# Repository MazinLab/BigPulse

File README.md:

# BigPulse
A high power avalanche mode laser driver

For fully isolated use, cut the jumper on the bottom, do not populate the boost converter and supply 200V and 12V to each side seperately

For use without ground isolation do not populate anything on the bottom other than the sense resistors and supply 12V through the barrel jack

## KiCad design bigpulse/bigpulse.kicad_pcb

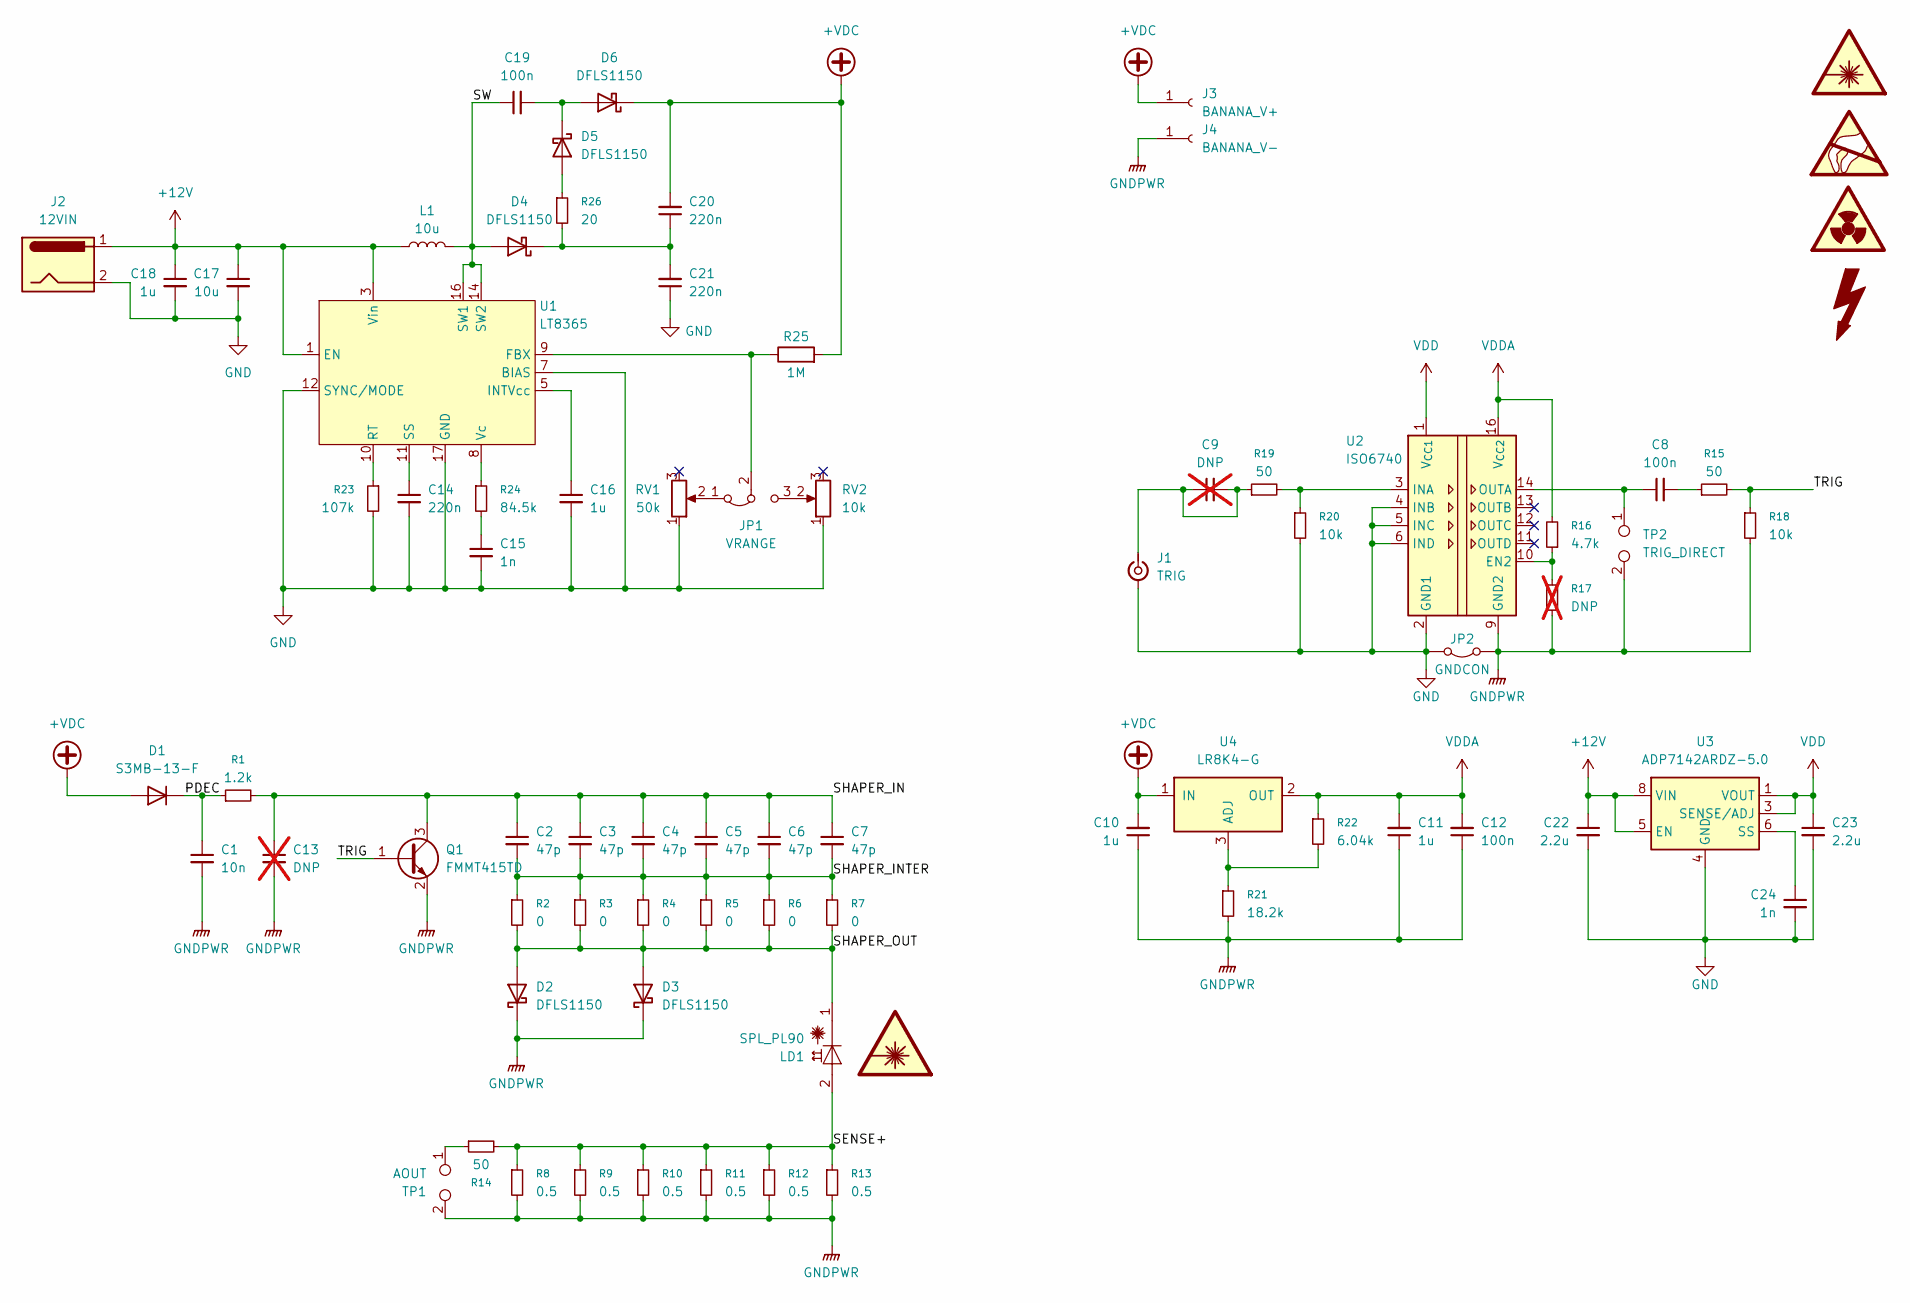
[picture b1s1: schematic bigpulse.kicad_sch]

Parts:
C1: 10n; C_1210_3225Metric; DIGIKEY_PN 709-VPDF102W103K1GV001ECT-ND
C2, C3, C4, C5, C6, C7: 47p; C_1210_3225Metric; DIGIKEY_PN 720-1040-1-ND
C8, C12, C19: 100n; C_1210_3225Metric; DIGIKEY_PN 445-2300-1-ND
C9: DNP; C_0603_1608Metric; not fitted
C10, C18: 1u; C_2220_5750Metric; DIGIKEY_PN 478-KGF55DR72J105KVCT-ND
C11, C16: 1u; C_0603_1608Metric; DIGIKEY_PN 1276-1946-1-ND
C13: DNP; C_1210_3225Metric; not fitted
C14: 220n; C_0603_1608Metric; DIGIKEY_PN 490-5402-1-ND
C15, C24: 1n; C_0603_1608Metric; DIGIKEY_PN 399-C0603C102K5RACTUCT-ND
C17: 10u; C_2220_5750Metric; DIGIKEY_PN 478-KGM55DR72A106MVCT-ND
C20, C21: 220n; C_2220_5750Metric; DIGIKEY_PN 490-3520-1-ND
C22, C23: 2.2u; C_0603_1608Metric; DIGIKEY_PN 490-GRM188Z71E225ME43DCT-ND
D1: S3MB-13-F; D_SMB; DIGIKEY_PN S3MB-FDICT-ND
D2, D3, D4, D5, D6: DFLS1150; D_PowerDI-123; DIGIKEY_PN DFLS1150Q-7DICT-ND
J1: TRIG; SMA_Amphenol_132134-10_Vertical; DIGIKEY_PN 132134-10
J2: 12VIN; BarrelJack_Wuerth_694106106102_2.0x5.5mm; DIGIKEY_PN 732-5929-1-ND
J3: BANANA_V+; MountingHole_3.7mm_Pad_Via; DIGIKEY_PN J10125-ND
J4: BANANA_V-; MountingHole_3.7mm_Pad_Via; DIGIKEY_PN J10126-ND
JP1: VRANGE; SolderJumper-3_P1.3mm_Bridged2Bar12_Pad1.0x1.5mm
JP2: GNDCON; SolderJumper-2_P1.3mm_Bridged_Pad1.0x1.5mm
L1: 10u; L_Wurth_WE-LQSH-4020; DIGIKEY_PN 732-3336-1-ND
LD1: SPL_PL90; LED_D5.0mm; DIGIKEY_PN 475-SPLPL90AT03-ND
Q1: FMMT415TD; SOT-23-3; DIGIKEY_PN FMMT415TDCT-ND
R1: 1.2k; R_1210_3225Metric; DIGIKEY_PN 2019-RK73B2ETTD122JCT-ND
R2, R3, R4, R5, R6, R7: 0; R_1210_3225Metric; DIGIKEY_PN RMCF1210ZT0R00CT-ND
R8, R9, R10, R11, R12, R13: 0.5; R_1210_3225Metric; DIGIKEY_PN 311-0.5NACT-ND
R14, R15, R19: 50; R_0603_1608Metric; DIGIKEY_PN 764-FC0603E50R0BTBST1CT-ND
R16: 4.7k; R_0603_1608Metric; DIGIKEY_PN 311-4.70KHRCT-ND
R17: DNP; R_0603_1608Metric; not fitted
R18, R20: 10k; R_0603_1608Metric; DIGIKEY_PN RMCF0603JT10K0CT-ND
R21: 18.2k; R_0603_1608Metric; DIGIKEY_PN RMCF0603FT18K2CT-ND
R22: 6.04k; R_0603_1608Metric; DIGIKEY_PN 2019-RK73H1JTTD6041FCT-ND
R23: 107k; R_0603_1608Metric; DIGIKEY_PN 311-107KHRCT-ND
R24: 84.5k; R_0603_1608Metric; DIGIKEY_PN 311-84.5KHRCT-ND
R25: 1M; R_0603_1608Metric; DIGIKEY_PN 2019-RN73H1JTTD1004B25CT-ND
R26: 20; R_0805_2012Metric; DIGIKEY_PN 738-RNCF0805DTE20R0CT-ND
RV1: 50k; Potentiometer_Bourns_3314S_Horizontal; DIGIKEY_PN 3314J-503ECT-ND
RV2: 10k; Potentiometer_Bourns_3314S_Horizontal; DIGIKEY_PN 3314J-103ECT-ND
TP1: AOUT; SMA_Amphenol_132134-10_Vertical; DIGIKEY_PN 132134-10
TP2: TRIG_DIRECT; SMA_Amphenol_132134-10_Vertical; DIGIKEY_PN 132134-10
U1: LT8365; Analog_MSOP-12-16-1EP_3x4.039mm_P0.5mm_EP1.651x2.845mm_Ther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; DIGIKEY_PN 505-LT8365EMSE#TRPBFCT-ND
U2: ISO6740; SOIC-16W_7.5x10.3mm_P1.27mm; DIGIKEY_PN 296-ISO6740QDWRQ1CT-ND
U3: ADP7142ARDZ-5.0; SOIC-8-1EP_3.9x4.9mm_P1.27mm_EP2.29x3mm; DIGIKEY_PN 505-ADP7142ARDZ-5.0-ND
U4: LR8K4-G; TO-252-2; DIGIKEY_PN LR8K4-GCT-ND

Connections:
+12V: C17.1, C18.1, C22.1, J2.1, L1.1, U1.1 (EN), U1.3 (Vin), U3.5 (EN), U3.7 (VIN), U3.8 (VIN)
+VDC: C10.2, C20.2, D1.2 (A), D6.1 (K), J3.1, R25.2, U4.1 (IN)
/PDEC: C1.1, D1.1 (K), R1.1
/SENSE+: LD1.2 (A), R8.1, R9.1, R10.1, R11.1, R12.1, R13.1, R14.2
/SHAPER_IN: C2.1, C3.1, C4.1, C5.1, C6.1, C7.1, C13.1, Q1.3 (C), R1.2
/SHAPER_INTER: C2.2, C3.2, C4.2, C5.2, C6.2, C7.2, R2.1, R3.1, R4.1, R5.1, R6.1, R7.1
/SHAPER_OUT: D2.2 (A), D3.2 (A), LD1.1 (C), R2.2, R3.2, R4.2, R5.2, R6.2, R7.2
/SW: C19.1, D4.2 (A), L1.2, U1.14 (SW2), U1.16 (SW1)
/TRIG: Q1.1 (B), R15.2, R18.1
GND: C14.2, C15.2, C16.2, C17.2, C18.2, C21.1, C22.2, C23.2, C24.2, J1.2 (Ext), J2.2, JP2.1 (A), R20.2, R23.2, RV1.1, RV2.1, U1.7 (BIAS), U1.12 (SYNC/MODE), U1.17 (GND), U2.2 (GND1), U2.4 (INB), U2.5 (INC), U2.6 (IND), U2.8 (GND1), U3.4 (GND), U3.9 (GND)
GNDPWR: C1.2, C10.1, C11.1, C12.1, C13.2, D2.1 (K), D3.1 (K), J4.1, JP2.2 (B), Q1.2 (E), R8.2, R9.2, R10.2, R11.2, R12.2, R13.2, R17.1, R18.2, R21.2, TP1.2, TP2.2, U2.9 (GND2), U2.15 (GND2)
unnamed: C8.2, R15.1
unnamed: C15.1, R24.2
unnamed: C20.1, C21.2, D4.1 (K), R26.2
unnamed: D5.2 (A), R26.1
unnamed: C19.2, D5.1 (K), D6.2 (A)
unnamed: C9.1, C9.2, J1.1 (In), R19.1
unnamed: JP1.1 (A), RV1.2
unnamed: JP1.3 (B), RV2.2
unnamed: JP1.2 (C), R25.1, U1.9 (FBX)
unnamed: R14.1, TP1.1
unnamed: C16.1, U1.5 (INTVcc)
unnamed: R23.1, U1.10 (RT)
unnamed: C14.1, U1.11 (SS)
unnamed: R24.1, U1.8 (Vc)
unnamed: R16.1, R17.2, U2.10 (EN2)
unnamed: R19.2, R20.1, U2.3 (INA)
unnamed: C8.1, TP2.1, U2.14 (OUTA)
unnamed: C24.1, U3.6 (SS)
unnamed: R21.1, R22.2, U4.3 (ADJ)
VDD: C23.1, U2.1 (V_{CC1}), U3.1 (VOUT), U3.2 (VOUT), U3.3 (SENSE/ADJ)
VDDA: C11.2, C12.2, R16.2, R22.1, U2.16 (V_{CC2}), U4.2 (OUT)

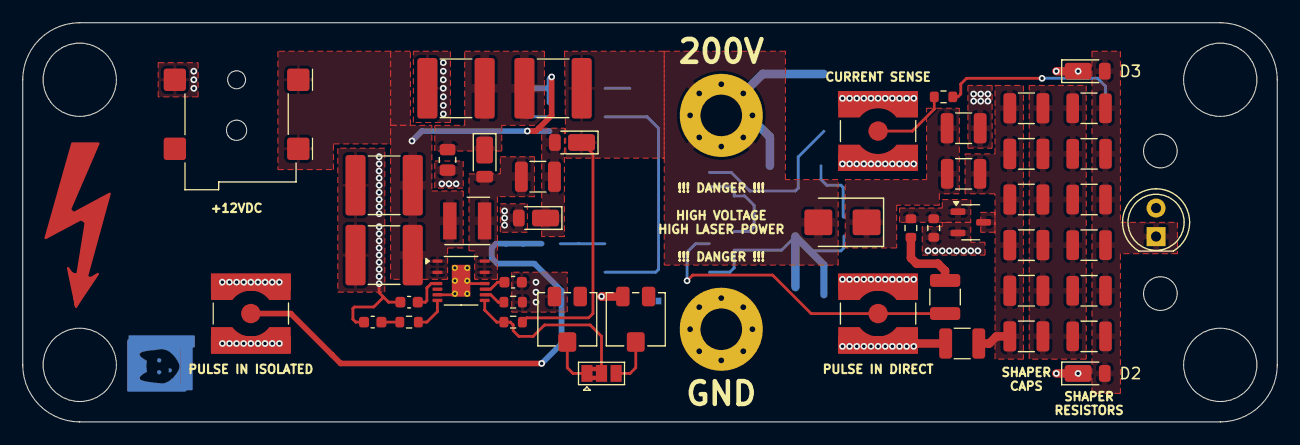
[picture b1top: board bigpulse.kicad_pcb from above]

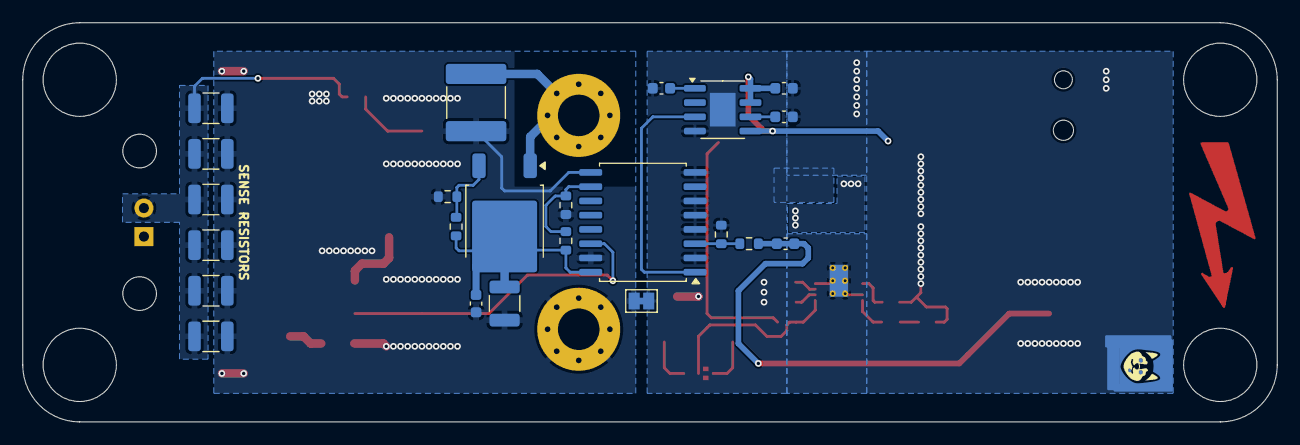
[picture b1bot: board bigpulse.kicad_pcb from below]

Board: 2 copper layers, 111.8 x 35.6 mm, 80 parts (24 on the bottom side), 32 nets.

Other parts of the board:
H**: 1/4 20; quarter-twenty
H**#2, H**#3, H**#4: 1/4 20; quarter-twenty
MH1, MH4: 4-40a; MountingHole_3mm
svg2mod: G***; milo

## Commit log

2025-09-18 Unmodified
2025-09-18 "Docs"
2025-09-21 Add Schematic PDF
